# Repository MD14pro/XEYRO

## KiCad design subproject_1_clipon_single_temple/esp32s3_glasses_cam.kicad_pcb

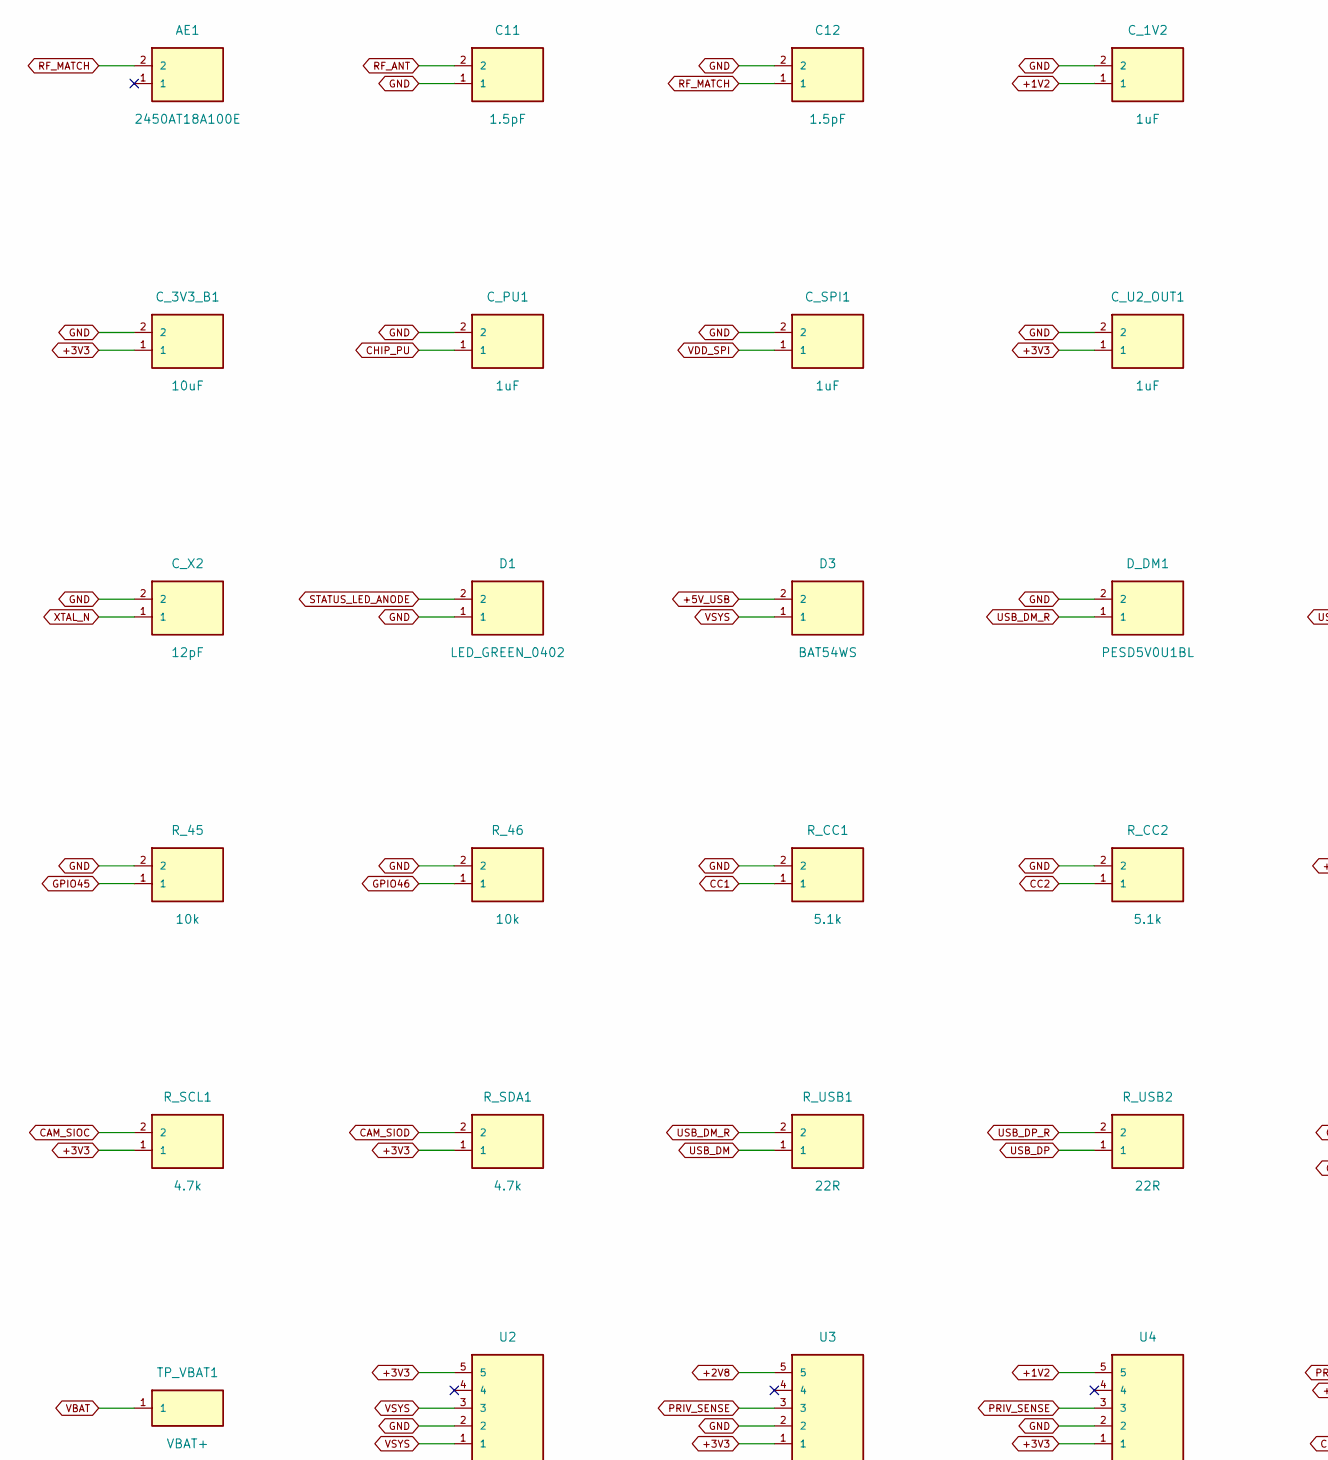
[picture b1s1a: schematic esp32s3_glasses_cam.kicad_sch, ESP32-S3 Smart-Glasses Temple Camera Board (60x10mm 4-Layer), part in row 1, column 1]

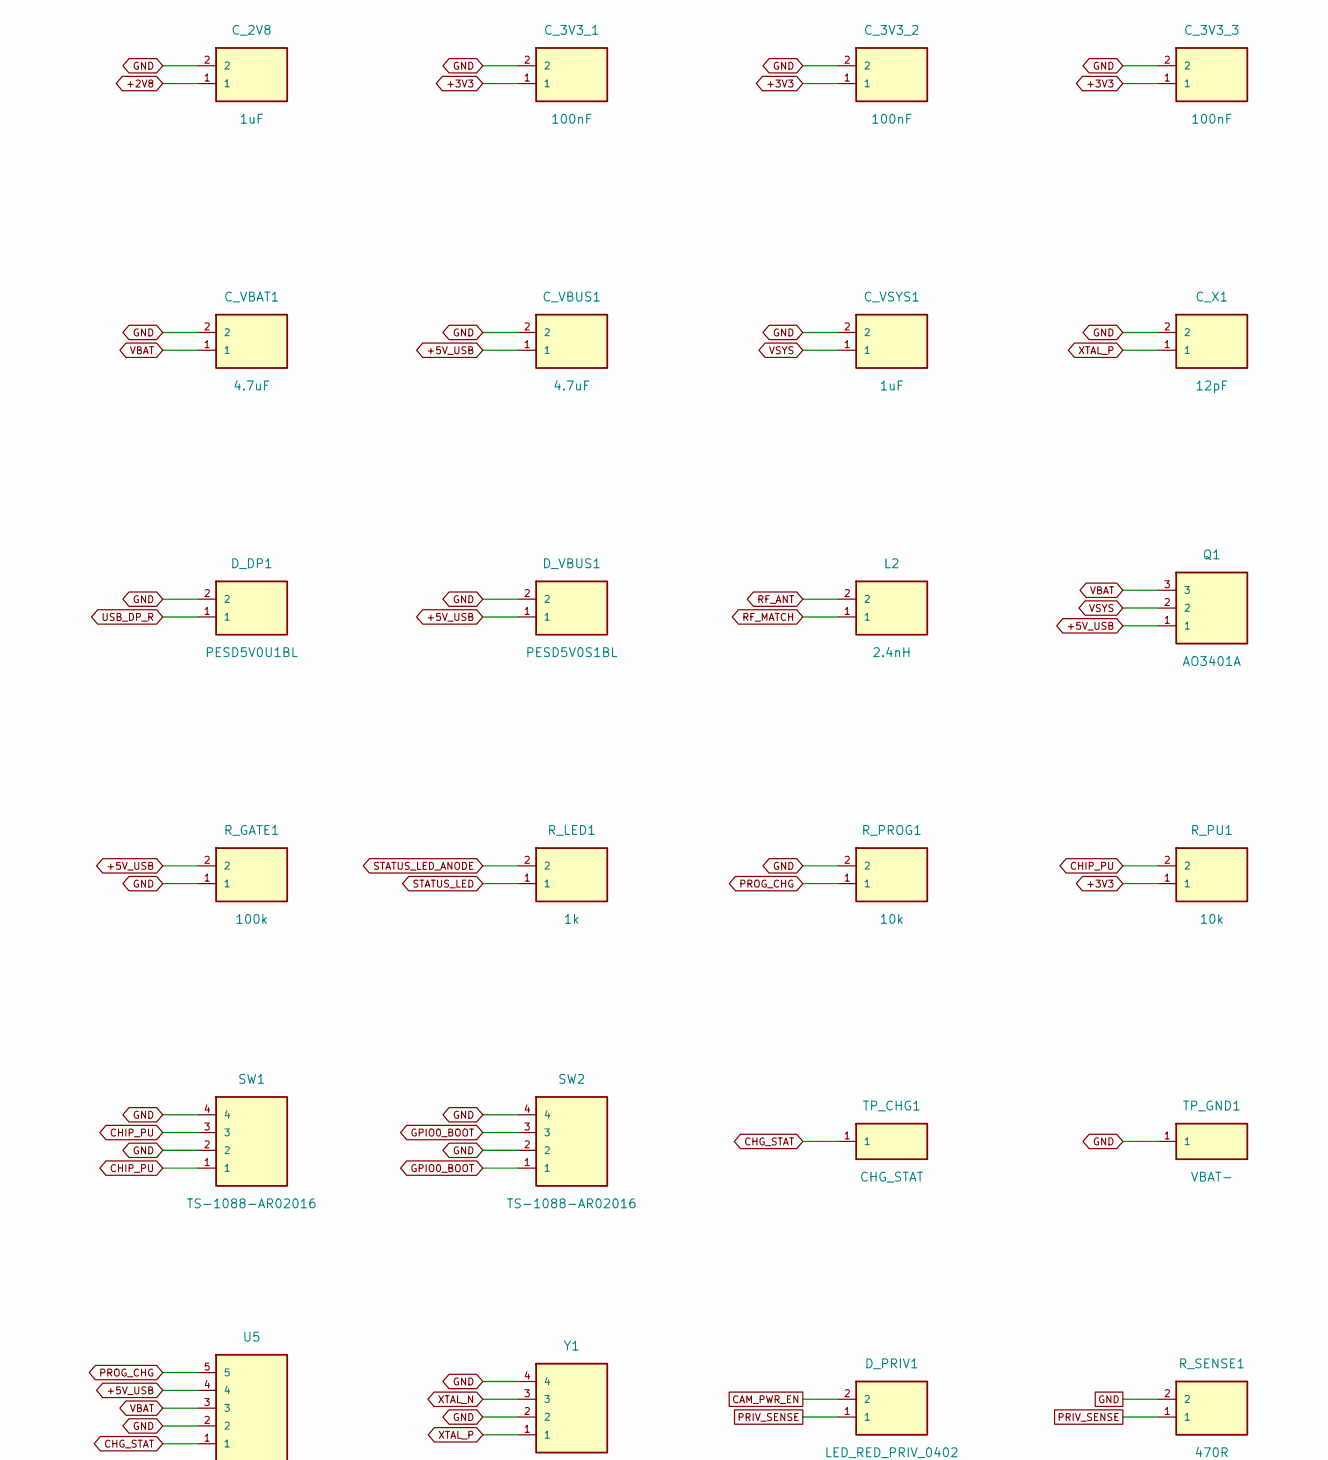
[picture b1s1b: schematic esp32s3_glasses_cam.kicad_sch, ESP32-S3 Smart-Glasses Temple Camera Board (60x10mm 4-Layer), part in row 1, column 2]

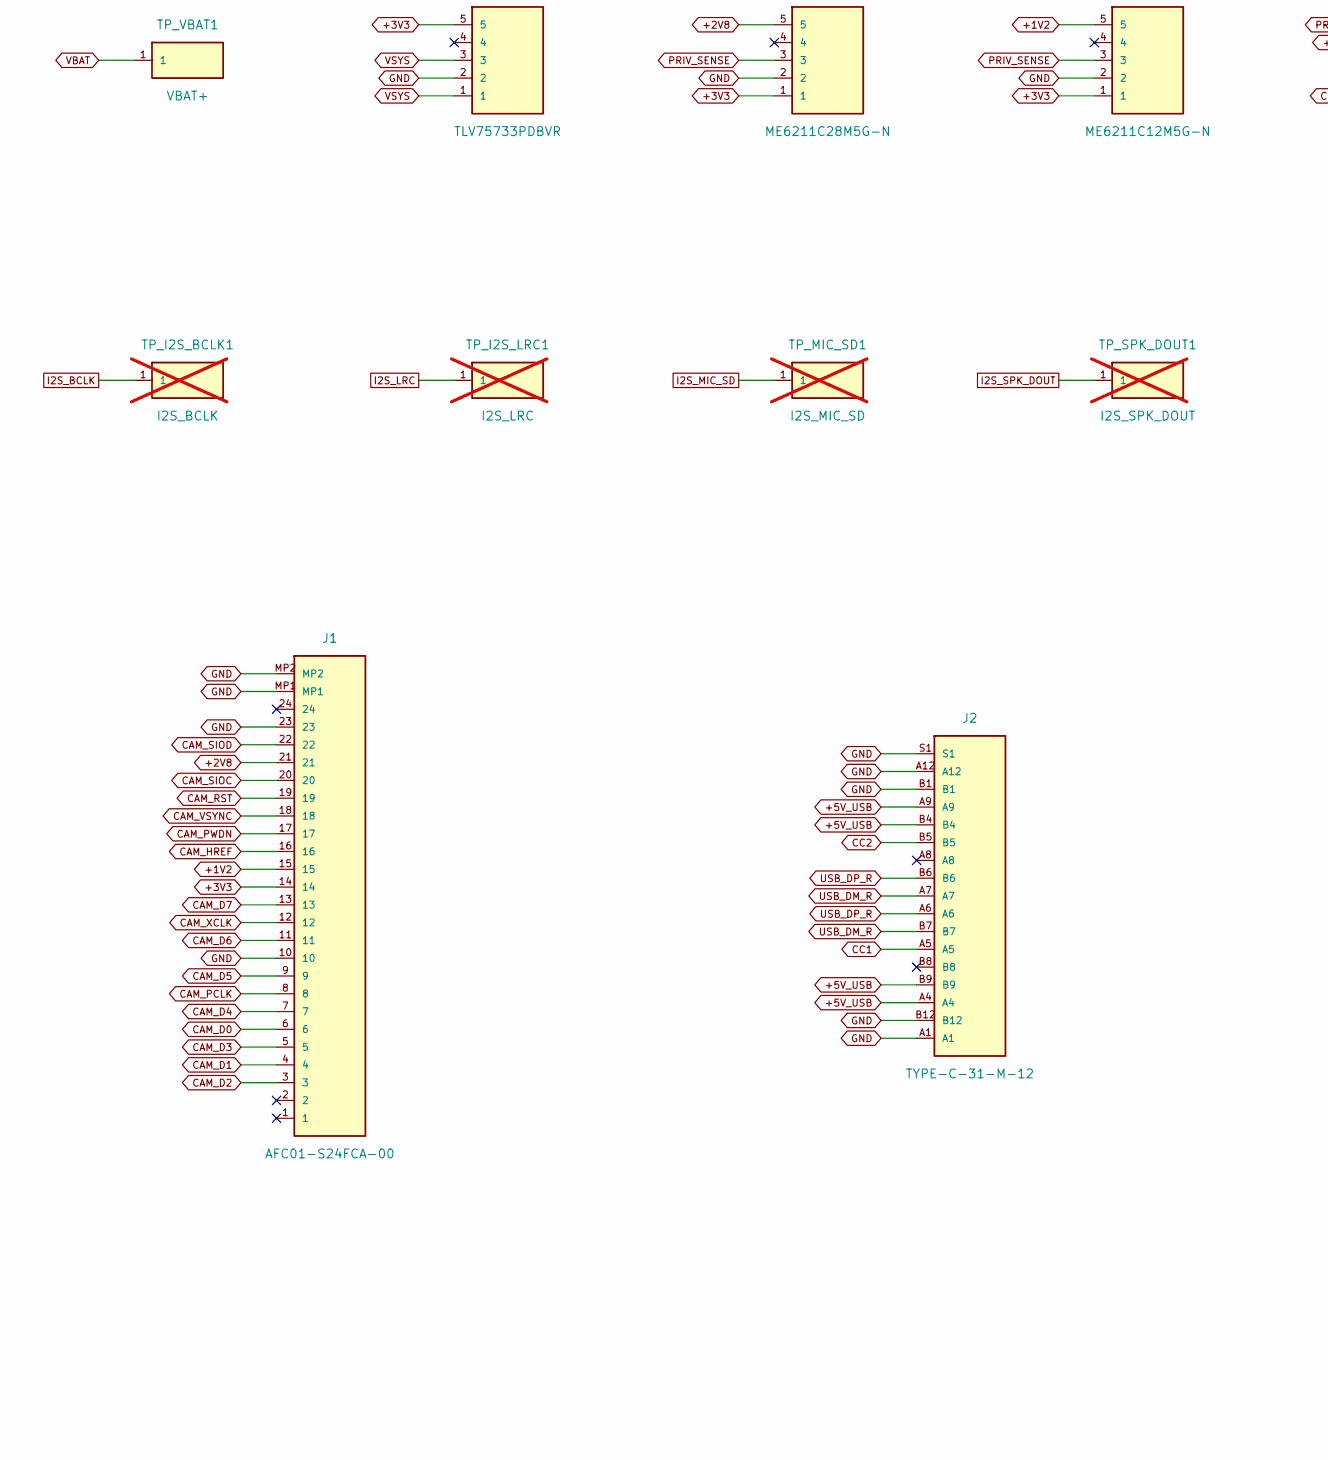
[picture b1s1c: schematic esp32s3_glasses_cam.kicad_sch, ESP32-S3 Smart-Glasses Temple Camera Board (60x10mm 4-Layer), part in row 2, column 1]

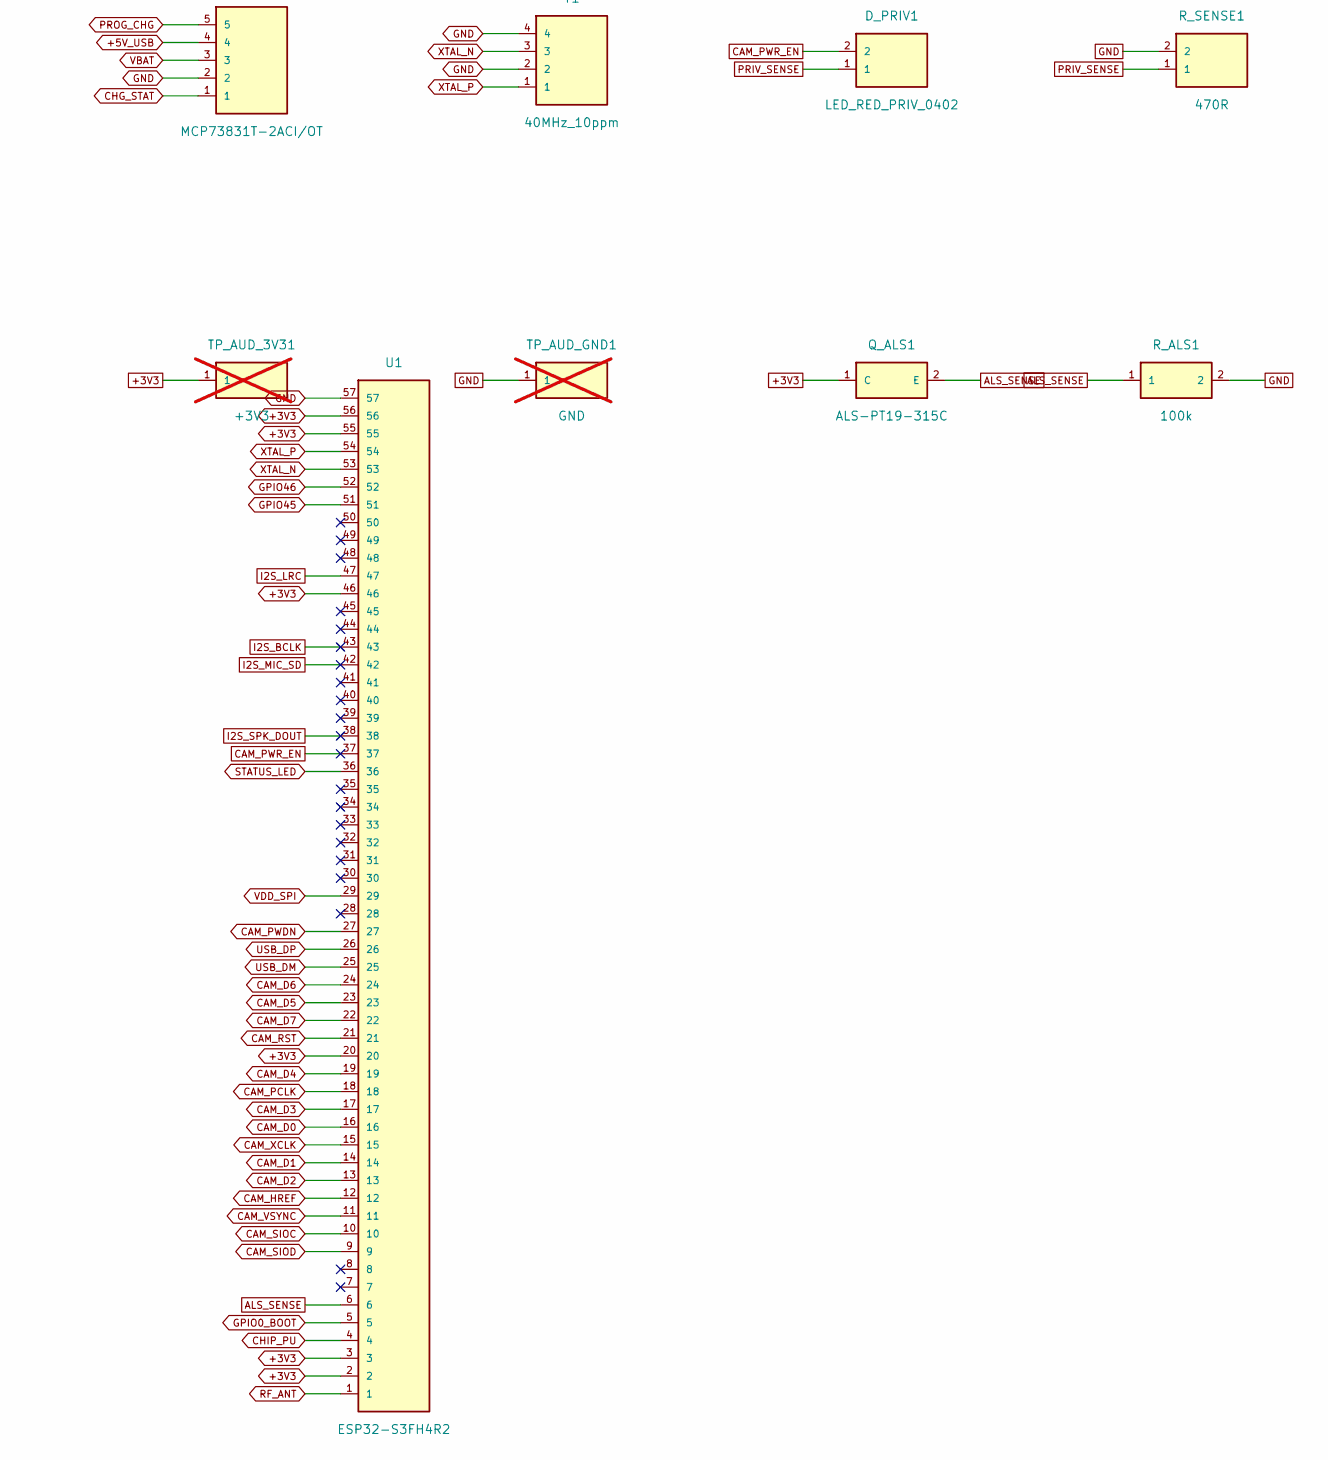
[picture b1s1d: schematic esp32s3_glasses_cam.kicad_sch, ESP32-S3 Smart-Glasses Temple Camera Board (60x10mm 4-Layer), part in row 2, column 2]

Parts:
AE1: 2450AT18A100E; Johanson_2450AT18A100E_3.2x1.6mm; MPN 2450AT18A100E; LCSC C89334
C11, C12: 1.5pF; C_0402_1005Metric; MPN GRM1555C1H1R5CA01D; LCSC C76958
C_1V2, C_2V8: 1uF; C_0402_1005Metric; MPN CL05A105KA5NQNC; LCSC C52923
C_3V3_1, C_3V3_2, C_3V3_3: 100nF; C_0402_1005Metric; MPN CL05B104KO5NNNC; LCSC C1525
C_3V3_B1: 10uF; C_0603_1608Metric; MPN CL10A106KP8NNNC; LCSC C19702
C_PU1: 1uF; C_0402_1005Metric; MPN CL05A105KA5NQNC; LCSC C52923
C_SPI1: 1uF; C_0402_1005Metric; MPN CL05A105KA5NQNC; LCSC C52923
C_U2_OUT1: 1uF; C_0402_1005Metric; MPN CL05A105KA5NQNC; LCSC C52923
C_VBAT1: 4.7uF; C_0603_1608Metric; MPN CL10A475KP8NNNC; LCSC C1705
C_VBUS1: 4.7uF; C_0603_1608Metric; MPN CL10A475KP8NNNC; LCSC C1705
C_VSYS1: 1uF; C_0402_1005Metric; MPN CL05A105KA5NQNC; LCSC C52923
C_X1, C_X2: 12pF; C_0402_1005Metric; MPN GRM1555C1H120JA01D; LCSC C1547
D1: LED_GREEN_0402; LED_0402_1005Metric; MPN 19-217/GHC-YR1S2/3T; LCSC C72043
D3: BAT54WS; D_SOD-323; MPN BAT54WS; LCSC C5251553
D_DM1: PESD5V0U1BL; D_SOD-882; MPN PESD5V0U1BL; LCSC C53477426
D_DP1: PESD5V0U1BL; D_SOD-882; MPN PESD5V0U1BL; LCSC C53477426
D_PRIV1: LED_RED_PRIV_0402; LED_0402_1005Metric; MPN 19-217/R6C-AL1M2VY/3T; LCSC C84256
D_VBUS1: PESD5V0S1BL; D_SOD-882; MPN PESD5V0S1BL,315; LCSC C84374
J1: AFC01-S24FCA-00; Jushuo_AFC01-S24FCA-00_1x24-1MP_P0.5mm_Horizontal; MPN AFC01-S24FCA-00; LCSC C262669
J2: TYPE-C-31-M-12; USB_C_Receptacle_HRO_TYPE-C-31-M-12; MPN TYPE-C-31-M-12; LCSC C165948
L2: 2.4nH; L_0402_1005Metric; MPN LQG15HS2N4S02D; LCSC C13607
Q1: AO3401A; SOT-23; MPN AO3401A; LCSC C15127
Q_ALS1: ALS-PT19-315C; C_0603_1608Metric; MPN ALS-PT19-315C/L177/TR8; LCSC C146233
R_45, R_46: 10k; R_0402_1005Metric; MPN 0402WGF1002TCE; LCSC C25744
R_ALS1: 100k; R_0402_1005Metric; MPN 0402WGF1003TCE; LCSC C25741
R_CC1, R_CC2: 5.1k; R_0402_1005Metric; MPN 0402WGF5101TCE; LCSC C25905
R_GATE1: 100k; R_0402_1005Metric; MPN 0402WGF1003TCE; LCSC C25741
R_LED1: 1k; R_0402_1005Metric; MPN 0402WGF1001TCE; LCSC C11702
R_PROG1: 10k; R_0402_1005Metric; MPN 0402WGF1002TCE; LCSC C25744
R_PU1: 10k; R_0402_1005Metric; MPN 0402WGF1002TCE; LCSC C25744
R_SCL1: 4.7k; R_0402_1005Metric; MPN 0402WGF4701TCE; LCSC C25900
R_SDA1: 4.7k; R_0402_1005Metric; MPN 0402WGF4701TCE; LCSC C25900
R_SENSE1: 470R; R_0402_1005Metric; MPN 0402WGF4700TCE; LCSC C25117
R_USB1, R_USB2: 22R; R_0402_1005Metric; MPN 0402WGF220JTCE; LCSC C25092
SW1, SW2: TS-1088-AR02016; XUNPU_TS-1088-AR02016_3.0x2.0mm; MPN TS-1088-AR02016; LCSC C720477
TP_AUD_3V31: +3V3; TestPad_0.8x0.8mm; MPN TP_SMD; not fitted
TP_AUD_GND1: GND; TestPad_0.8x0.8mm; MPN TP_SMD; not fitted
TP_CHG1: CHG_STAT; TestPad_0.8x0.8mm; MPN TP_SMD
TP_GND1: VBAT-; WirePad_1.4x1.6mm; MPN TP_SMD
TP_I2S_BCLK1: I2S_BCLK; TestPad_0.8x0.8mm; MPN TP_SMD; not fitted
TP_I2S_LRC1: I2S_LRC; TestPad_0.8x0.8mm; MPN TP_SMD; not fitted
TP_MIC_SD1: I2S_MIC_SD; TestPad_0.8x0.8mm; MPN TP_SMD; not fitted
TP_SPK_DOUT1: I2S_SPK_DOUT; TestPad_0.8x0.8mm; MPN TP_SMD; not fitted
TP_VBAT1: VBAT+; WirePad_1.4x1.6mm; MPN TP_SMD
U1: ESP32-S3FH4R2; Espressif_QFN-56-1EP_7x7mm_P0.4mm_EP4.0x4.0mm; MPN ESP32-S3FH4R2; LCSC C3013940
U2: TLV75733PDBVR; SOT-23-5; MPN TLV75733PDBVR; LCSC C485517
U3: ME6211C28M5G-N; SOT-23-5; MPN ME6211C28M5G-N; LCSC C53099
U4: ME6211C12M5G-N; SOT-23-5; MPN ME6211C12M5G-N; LCSC C236672
U5: MCP73831T-2ACI/OT; SOT-23-5; MPN MCP73831T-2ACI/OT; LCSC C424093
Y1: 40MHz_10ppm; Murata_XRCGB40M000F2P00R0_2.0x1.6mm_4Pin; MPN XRCGB40M000F2P00R0; LCSC C2843083

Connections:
+1V2: C_1V2.1, J1.15, U4.5
+2V8: C_2V8.1, J1.21, U3.5
+3V3: C_3V3_1.1, C_3V3_2.1, C_3V3_3.1, C_3V3_B1.1, C_U2_OUT1.1, J1.14, Q_ALS1.1 (C), R_PU1.1, R_SCL1.1, R_SDA1.1, TP_AUD_3V31.1, U1.2, U1.3, U1.20, U1.46, U1.55, U1.56, U2.5, U3.1, U4.1
+5V_USB: C_VBUS1.1, D3.2, D_VBUS1.1, J2.A4, J2.A9, J2.B4, J2.B9, Q1.1, R_GATE1.2, U5.4
ALS_SENSE: Q_ALS1.2 (E), R_ALS1.1, U1.6
CAM_D0: J1.6, U1.16
CAM_D1: J1.4, U1.14
CAM_D2: J1.3, U1.13
CAM_D3: J1.5, U1.17
CAM_D4: J1.7, U1.19
CAM_D5: J1.9, U1.23
CAM_D6: J1.11, U1.24
CAM_D7: J1.13, U1.22
CAM_HREF: J1.16, U1.12
CAM_PCLK: J1.8, U1.18
CAM_PWDN: J1.17, U1.27
CAM_PWR_EN: D_PRIV1.2, U1.37
CAM_RST: J1.19, U1.21
CAM_SIOC: J1.20, R_SCL1.2, U1.10
CAM_SIOD: J1.22, R_SDA1.2, U1.9
CAM_VSYNC: J1.18, U1.11
CAM_XCLK: J1.12, U1.15
CC1: J2.A5, R_CC1.1
CC2: J2.B5, R_CC2.1
CHG_STAT: TP_CHG1.1, U5.1
CHIP_PU: C_PU1.1, R_PU1.2, SW1.1, SW1.3, U1.4
GND: C11.1, C12.2, C_1V2.2, C_2V8.2, C_3V3_1.2, C_3V3_2.2, C_3V3_3.2, C_3V3_B1.2, C_PU1.2, C_SPI1.2, C_U2_OUT1.2, C_VBAT1.2, C_VBUS1.2, C_VSYS1.2, C_X1.2, C_X2.2, D1.1, D_DM1.2, D_DP1.2, D_VBUS1.2, J1.10, J1.23, J1.MP1, J1.MP2, J2.A1, J2.A12, J2.B1, J2.B12, J2.S1, R_45.2, R_46.2, R_ALS1.2, R_CC1.2, R_CC2.2, R_GATE1.1, R_PROG1.2, R_SENSE1.2, SW1.2, SW1.4, SW2.2, SW2.4, TP_AUD_GND1.1, TP_GND1.1, U1.57, U2.2, U3.2, U4.2, U5.2, Y1.2, Y1.4
GPIO0_BOOT: SW2.1, SW2.3, U1.5
GPIO45: R_45.1, U1.51
GPIO46: R_46.1, U1.52
I2S_BCLK: TP_I2S_BCLK1.1, U1.43
I2S_LRC: TP_I2S_LRC1.1, U1.47
I2S_MIC_SD: TP_MIC_SD1.1, U1.42
I2S_SPK_DOUT: TP_SPK_DOUT1.1, U1.38
PRIV_SENSE: D_PRIV1.1, R_SENSE1.1, U3.3, U4.3
PROG_CHG: R_PROG1.1, U5.5
RF_ANT: C11.2, L2.2, U1.1
RF_MATCH: AE1.2, C12.1, L2.1
STATUS_LED: R_LED1.1, U1.36
STATUS_LED_ANODE: D1.2, R_LED1.2
USB_DM: R_USB1.1, U1.25
USB_DM_R: D_DM1.1, J2.A7, J2.B7, R_USB1.2
USB_DP: R_USB2.1, U1.26
USB_DP_R: D_DP1.1, J2.A6, J2.B6, R_USB2.2
VBAT: C_VBAT1.1, Q1.3, TP_VBAT1.1, U5.3
VDD_SPI: C_SPI1.1, U1.29
VSYS: C_VSYS1.1, D3.1, Q1.2, U2.1, U2.3
XTAL_N: C_X2.1, U1.53, Y1.3
XTAL_P: C_X1.1, U1.54, Y1.1

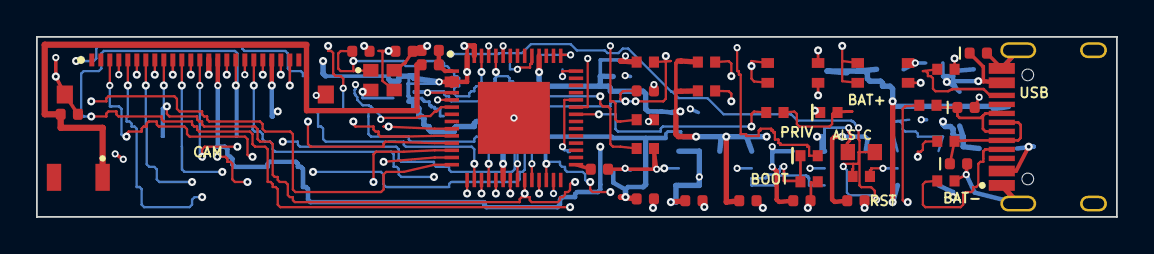
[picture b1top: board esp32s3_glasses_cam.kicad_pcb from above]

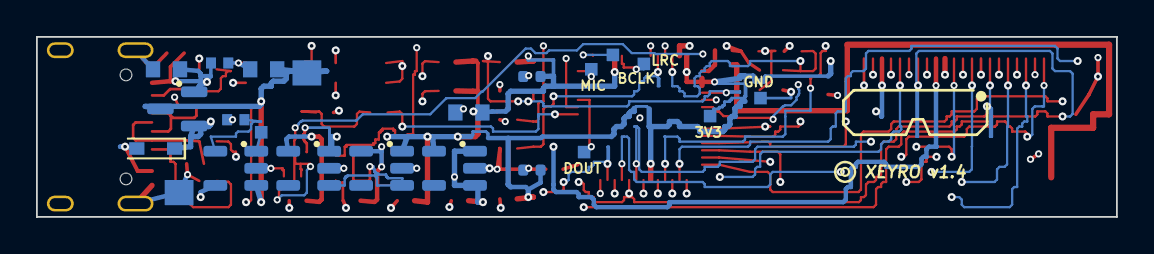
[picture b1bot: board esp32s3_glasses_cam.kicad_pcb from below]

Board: 4 copper layers, 60.0 x 10.0 mm, 59 parts (22 on the bottom side), 49 nets.

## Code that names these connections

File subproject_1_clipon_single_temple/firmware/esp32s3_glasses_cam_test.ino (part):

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// ============================================================================
// 1. EXACT PCB GPIO PIN DEFINITIONS (MATCHING esp32s3_glasses_cam.kicad_sch)
// ============================================================================
#define CAM_PIN_PWDN    21   // U1 Pin 27 (GPIO21) -> J1 Pin 17 (CAM_PWDN)
#define CAM_PIN_RESET   15   // U1 Pin 21 (GPIO15) -> J1 Pin 19 (CAM_RST)
#define CAM_PIN_XCLK    10   // U1 Pin 15 (GPIO10) -> J1 Pin 12 (CAM_XCLK)
#define CAM_PIN_SIOD     4   // U1 Pin 9  (GPIO4)  -> J1 Pin 22 (CAM_SIOD / SDA)
#define CAM_PIN_SIOC     5   // U1 Pin 10 (GPIO5)  -> J1 Pin 20 (CAM_SIOC / SCL)

#define CAM_PIN_D0      11   // U1 Pin 16 (GPIO11) -> J1 Pin 6  (CAM_D0 / Y2)
#define CAM_PIN_D1       9   // U1 Pin 14 (GPIO9)  -> J1 Pin 4  (CAM_D1 / Y3)
#define CAM_PIN_D2       8   // U1 Pin 13 (GPIO8)  -> J1 Pin 3  (CAM_D2 / Y4)
#define CAM_PIN_D3      12   // U1 Pin 17 (GPIO12) -> J1 Pin 5  (CAM_D3 / Y5)
#define CAM_PIN_D4      14   // U1 Pin 19 (GPIO14) -> J1 Pin 7  (CAM_D4 / Y6)
#define CAM_PIN_D5      17   // U1 Pin 23 (GPIO17) -> J1 Pin 9  (CAM_D5 / Y7)
#define CAM_PIN_D6      18   // U1 Pin 24 (GPIO18) -> J1 Pin 11 (CAM_D6 / Y8)
#define CAM_PIN_D7      16   // U1 Pin 22 (GPIO16) -> J1 Pin 13 (CAM_D7 / Y9)

#define CAM_PIN_VSYNC    6   // U1 Pin 11 (GPIO6)  -> J1 Pin 18 (CAM_VSYNC)
#define CAM_PIN_HREF     7   // U1 Pin 12 (GPIO7)  -> J1 Pin 16 (CAM_HREF)
#define CAM_PIN_PCLK    13   // U1 Pin 18 (GPIO13) -> J1 Pin 8  (CAM_PCLK)

#define PIN_ALS_SENSE   1    // U1 Pin 6 (GPIO1 / ADC1_CH0) -> Q_ALS1 (ALS-PT19-315C + 100k) Anti-Tape Light Sensor
#define PIN_CAM_PWR_EN  47   // U1 Pin 37 (GPIO47) -> D_PRIV1 (Hardware Privacy LED) -> U3/U4 EN
#define PIN_STATUS_LED  48   // U1 Pin 36 (GPIO48) -> R_LED1 (1k) -> D1 Anode
#define PIN_I2S_BCLK    38   // U1 Pin 43 (GPIO38) -> TP_I2S_BCLK1 (Speaker/Mic Bit Clock)
#define PIN_I2S_LRC     41   // U1 Pin 47 (GPIO41) -> TP_I2S_LRC1  (Speaker/Mic Word Select)
#define PIN_I2S_DOUT    33   // U1 Pin 38 (GPIO33) -> TP_SPK_DOUT1 (Down-Firing Speaker I2S Data)
#define PIN_I2S_MIC_SD  37   // U1 Pin 42 (GPIO37) -> TP_MIC_SD1   (MEMS Mic I2S Data)
#define PIN_BOOT_BTN     0   // U1 Pin 5  (GPIO0)  -> SW2 Active-Low BOOT Button (SW1 is RESET on CHIP_PU)

// Optional Wi-Fi credentials (falls back to SoftAP "GlassesCam-S3" if not found)
const char* WIFI_SSID = "YOUR_WIFI_SSID";
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      last_als_chk = millis();
      if (isPrivacyLedTampered()) {
        Serial.println("[PRIVACY] TAMPER DETECTED (LED window covered in bright scene) — cutting camera power!");
        digitalWrite(PIN_CAM_PWR_EN, LOW); // Hardware-enforced interlock cuts +2V8/+1V2 LDOs
        res = ESP_FAIL;
        break;
      }
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  }

  // Check 2: Toggle Status LED (GPIO48 -> R_LED1 (1k) -> D1)
  pinMode(PIN_CAM_PWR_EN, OUTPUT);
  digitalWrite(PIN_CAM_PWR_EN, HIGH); // Hardware-enforced: powers D_PRIV1 + OV2640 rails (+2V8/+1V2)
  delay(20);
  pinMode(PIN_STATUS_LED, OUTPUT);
  pinMode(PIN_BOOT_BTN, INPUT_PULLUP);
  for (int i = 0; i < 3; i++) {
    digitalWrite(PIN_STATUS_LED, HIGH);
    delay(80);
    digitalWrite(PIN_STATUS_LED, LOW);
    delay(80);
  }
  Serial.println("[PASS] Status LED (GPIO48 -> D1) blinked 3x.");
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  // Capture 1 test frame to verify all 8 DVP data lines (D0..D7) + PCLK/VSYNC/HREF
  camera_fb_t *fb = esp_camera_fb_get();
  if (!fb || fb->len == 0) {
    Serial.println("[FAIL] Test frame capture returned empty buffer! Check CAM_PCLK (GPIO13).");
    return false;
  }
  Serial.printf("[PASS] Captured test JPEG frame (%u bytes, %ux%u).\n",
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void setup() {
  Serial.begin(115200);
  analogReadResolution(12);
  analogSetPinAttenuation(PIN_ALS_SENSE, ADC_11db);
  delay(1500); // Allow Native USB CDC enumeration on GPIO19/GPIO20

  bool cam_ok = runHardwareSelfTest();
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
  if (cam_ok) {
    startCameraServer();
    digitalWrite(PIN_STATUS_LED, HIGH); // Solid LED = streaming ready
  }
}

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static int  tamper_clear_streak    = 0;

bool isPrivacyLedTampered() {
  int als_mv = analogReadMilliVolts(PIN_ALS_SENSE);
  sensor_t *s = esp_camera_sensor_get();
  if (!s) return false;

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    static uint32_t last_rec_chk = 0;
    if (millis() - last_rec_chk > 1000) {
      last_rec_chk = millis();
      int als_mv = analogReadMilliVolts(PIN_ALS_SENSE);
      if (als_mv >= ALS_CLEAR_MV_THRESH) {
        tamper_clear_streak++;
        if (tamper_clear_streak >= CLEAR_CONFIRM_COUNT) {
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          privacy_tamper_latched = false;
          tamper_hit_streak = 0;
          tamper_clear_streak = 0;
          digitalWrite(PIN_CAM_PWR_EN, HIGH);
          delay(100);
          esp_camera_deinit();
          runHardwareSelfTest();
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      Serial.println("[PRIVACY] Manual BOOT recovery requested — re-checking camera.");
      privacy_tamper_latched = false;
      tamper_hit_streak = 0;
      digitalWrite(PIN_CAM_PWR_EN, HIGH);
      delay(100);
      esp_camera_deinit();
      runHardwareSelfTest();
    } else {
      Serial.printf("[STAT] Free Heap: %u | Free PSRAM: %u | Wi-Fi RSSI: %d dBm | ALS: %d mV\n",
                    ESP.getFreeHeap(), ESP.getFreePsram(), WiFi.RSSI(), analogReadMilliVolts(PIN_ALS_SENSE));
    }
    delay(500);
  }
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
